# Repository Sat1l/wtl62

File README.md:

# wtl62

#### Hardware disclaimer
The folder structure is fucked up and probably wont be fixed as i see no reason for this.
Top case part (plate) is located in the bottom case part folder, and this one is located in the general pcb folder. Yeah.
There's also Willing To Live Better 62 inside, but this one proly wont' see a light of day as there prolly aint no interest in this design. Have fun.

#### firmware use guide
clone wtl62 folder to qmk_firmware/keyboards
#### Compiling
`qmk compile -kb WTL62 -km keymap`
- replace keymap with keymap you would like to compile. This repo contains only default keymap
#### Flashing default .hex file
[QMK Toolbox](https://github.com/qmk/qmk_toolbox) is the easiest way to do this. Short pins `gnd` and `rst` on yours MCU to reset
#### Using Vial
1. Flash `wtl62_via.hex` file to the keyboard
2. Open Vial
3. Go to File>Sideload VIA JSON...
4. Select `via.json` file
5. Voila! Now you can configure wtl62 using Vial

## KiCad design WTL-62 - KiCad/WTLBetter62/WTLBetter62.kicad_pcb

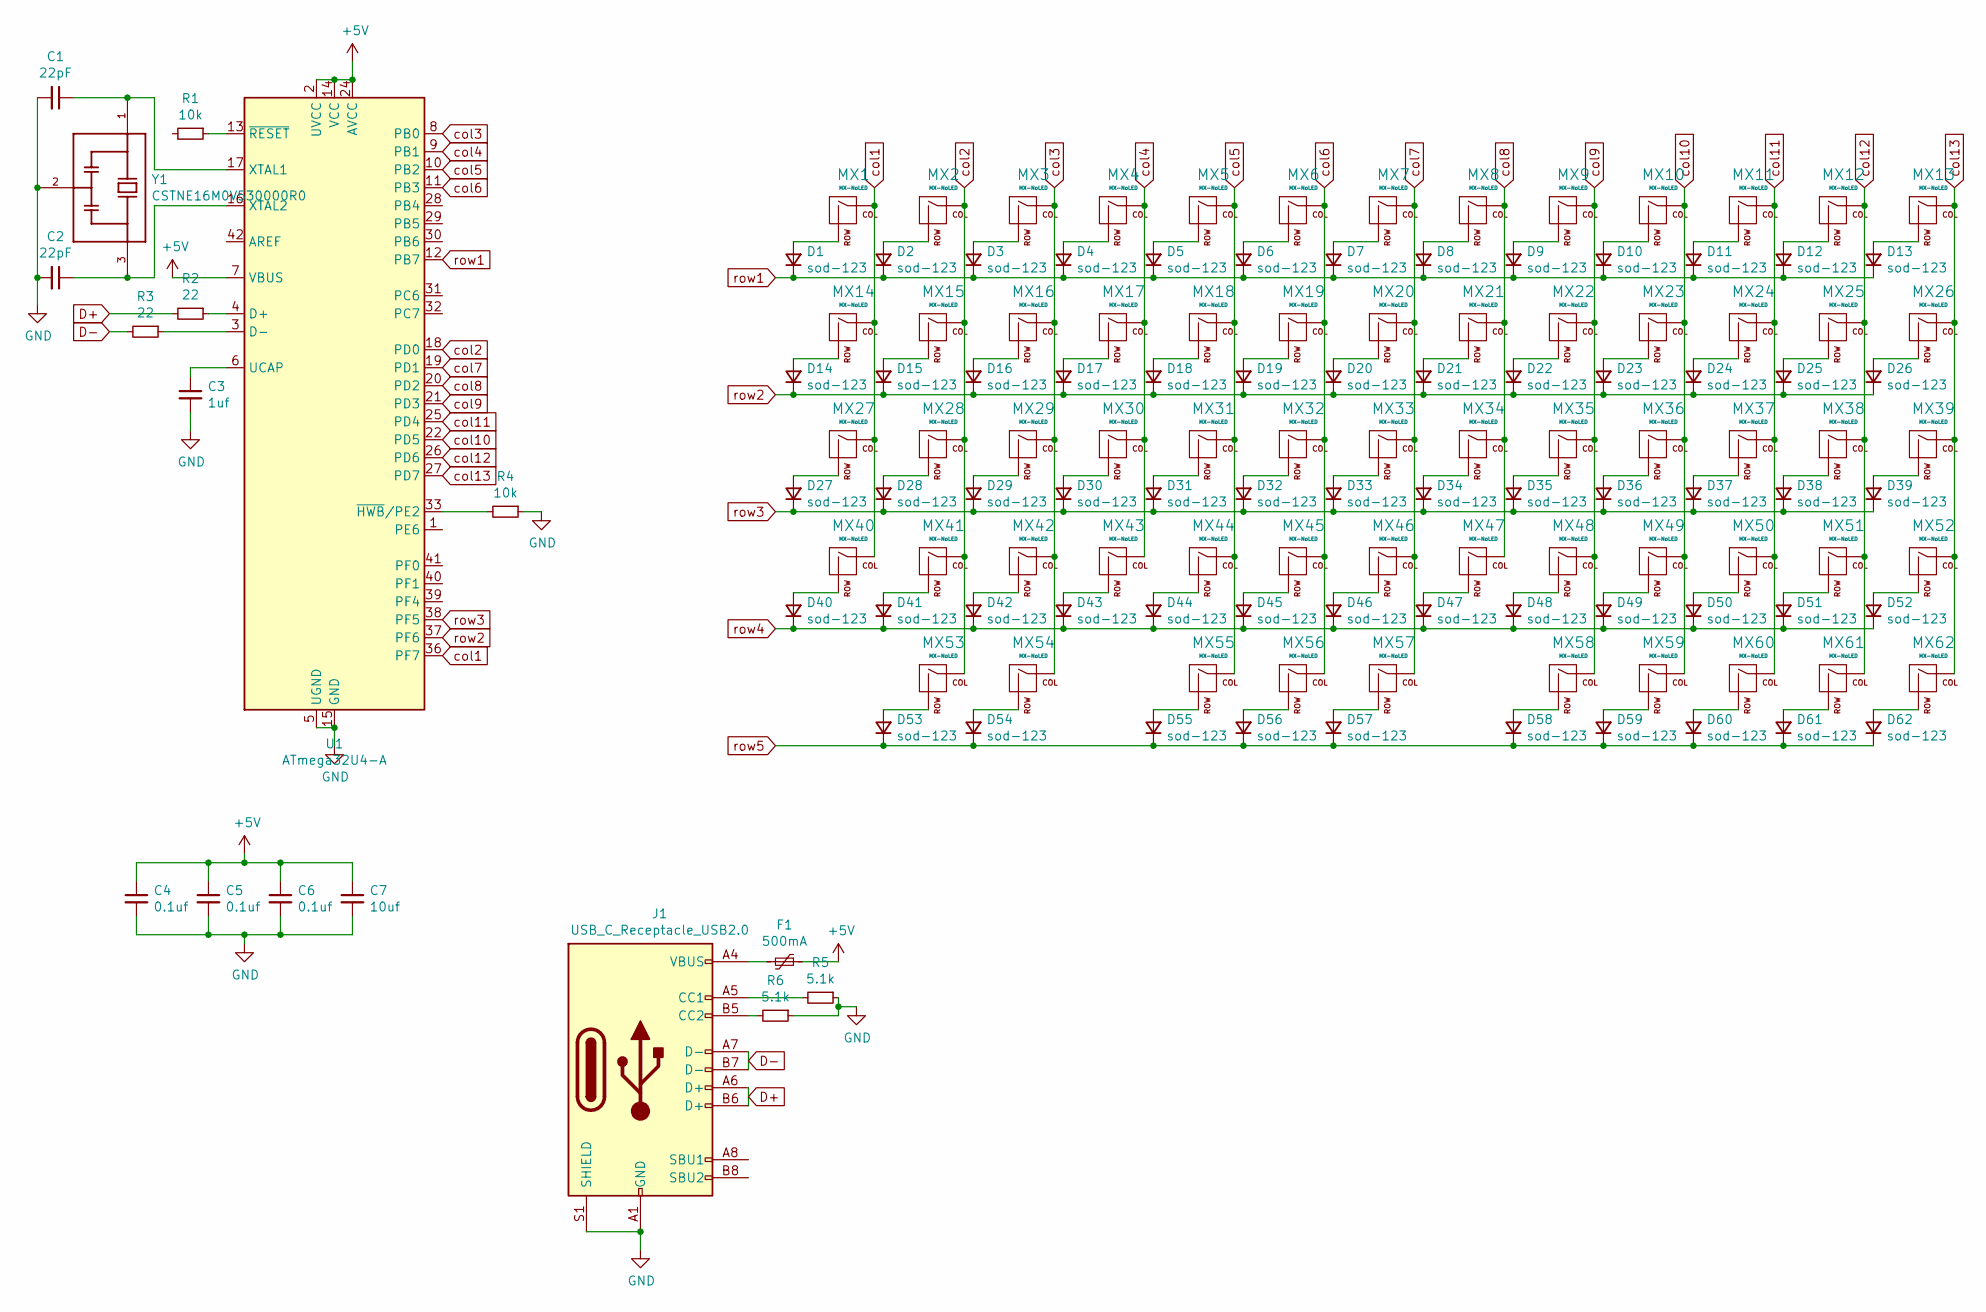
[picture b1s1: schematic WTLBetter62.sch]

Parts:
C1, C2: 22pF; C_0805_2012Metric
C3: 1uf; C_0805_2012Metric
C4, C5, C6: 0.1uf; C_0805_2012Metric
C7: 10uf; C_0805_2012Metric
D1, D2, D3, D4, D5, D6, D7, D8, D9, D10, D11, D12, D13, D14, D15, D16, D17, D18, D19, D20, D21, D22, D23, D24, D25, D26, D27, D28, D29, D30, D31, D32, D33, D34, D35, D36, D37, D38, D39, D40, D41, D42, D43, D44, D45, D46, D47, D48, D49, D50, D51, D52, D53, D54, D55, D56, D57, D58, D59, D60, D61, D62: sod-123; D3_SMD_v2
F1: 500mA; Fuse_1206_3216Metric
J1: USB_C_Receptacle_USB2.0; easyeda_C168688
MX1, MX2, MX3, MX4, MX5, MX6, MX7, MX8, MX9, MX10, MX11, MX12, MX13, MX14, MX15, MX16, MX17, MX18, MX19, MX20, MX21, MX22, MX23, MX24, MX25, MX26, MX27, MX28, MX29, MX30, MX31, MX32, MX33, MX34, MX35, MX36, MX37, MX38, MX39, MX40, MX41, MX42, MX43, MX44, MX45, MX46, MX47, MX48, MX49, MX50, MX51, MX52, MX53, MX54, MX55, MX56, MX57, MX58, MX59, MX60, MX61, MX62: MX-NoLED; CherryMX_Hotswap
R1, R4: 10k; R_0805_2012Metric
R2, R3: 22; R_0805_2012Metric
R5, R6: 5.1k; R_0805_2012Metric
U1: ATmega32U4-A; TQFP-44_10x10mm_P0.8mm
Y1: CSTNE16M0V530000R0; OSC_CSTNE16M0V530000R0; PARTREV JGC42-8853B

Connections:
+5V: C4.1, C5.1, C6.1, C7.1, F1.1, U1.2 (UVCC), U1.7 (VBUS), U1.14 (VCC), U1.24 (AVCC), U1.34 (VCC), U1.44 (AVCC)
D+: J1.A6 (D+), J1.B6 (D+), R2.2
D-: J1.A7 (D-), J1.B7 (D-), R3.2
GND: C1.2, C2.2, C3.2, C4.2, C5.2, C6.2, C7.2, J1.A1 (GND), J1.A12 (GND), J1.B1 (GND), J1.B12 (GND), J1.S1 (SHIELD), R4.1, R5.1, R6.1, U1.5 (UGND), U1.15 (GND), U1.23 (GND), U1.35 (GND), U1.43 (GND), Y1.2
unnamed: C1.1, U1.17 (XTAL1), Y1.1
unnamed: C2.1, U1.16 (XTAL2), Y1.3
unnamed: C3.1, U1.6 (UCAP)
unnamed: D1.2 (A), MX1.2 (ROW)
unnamed: D2.2 (A), MX2.2 (ROW)
unnamed: D3.2 (A), MX3.2 (ROW)
unnamed: D4.2 (A), MX4.2 (ROW)
unnamed: D5.2 (A), MX5.2 (ROW)
unnamed: D6.2 (A), MX6.2 (ROW)
unnamed: D7.2 (A), MX7.2 (ROW)
unnamed: D8.2 (A), MX8.2 (ROW)
unnamed: D9.2 (A), MX9.2 (ROW)
unnamed: D10.2 (A), MX10.2 (ROW)
unnamed: D11.2 (A), MX11.2 (ROW)
unnamed: D12.2 (A), MX12.2 (ROW)
unnamed: D13.2 (A), MX13.2 (ROW)
unnamed: D14.2 (A), MX14.2 (ROW)
unnamed: D15.2 (A), MX15.2 (ROW)
unnamed: D16.2 (A), MX16.2 (ROW)
unnamed: D17.2 (A), MX17.2 (ROW)
unnamed: D18.2 (A), MX18.2 (ROW)
unnamed: D19.2 (A), MX19.2 (ROW)
unnamed: D20.2 (A), MX20.2 (ROW)
unnamed: D21.2 (A), MX21.2 (ROW)
unnamed: D22.2 (A), MX22.2 (ROW)
unnamed: D23.2 (A), MX23.2 (ROW)
unnamed: D24.2 (A), MX24.2 (ROW)
unnamed: D25.2 (A), MX25.2 (ROW)
unnamed: D26.2 (A), MX26.2 (ROW)
unnamed: D27.2 (A), MX27.2 (ROW)
unnamed: D28.2 (A), MX28.2 (ROW)
unnamed: D29.2 (A), MX29.2 (ROW)
unnamed: D30.2 (A), MX30.2 (ROW)
unnamed: D31.2 (A), MX31.2 (ROW)
unnamed: D32.2 (A), MX32.2 (ROW)
unnamed: D33.2 (A), MX33.2 (ROW)
unnamed: D34.2 (A), MX34.2 (ROW)
unnamed: D35.2 (A), MX35.2 (ROW)
unnamed: D36.2 (A), MX36.2 (ROW)
unnamed: D37.2 (A), MX37.2 (ROW)
unnamed: D38.2 (A), MX38.2 (ROW)
unnamed: D39.2 (A), MX39.2 (ROW)
unnamed: D40.2 (A), MX40.2 (ROW)
unnamed: D41.2 (A), MX41.2 (ROW)
unnamed: D42.2 (A), MX42.2 (ROW)
unnamed: D43.2 (A), MX43.2 (ROW)
unnamed: D44.2 (A), MX44.2 (ROW)
unnamed: D45.2 (A), MX45.2 (ROW)
unnamed: D46.2 (A), MX46.2 (ROW)
unnamed: D47.2 (A), MX47.2 (ROW)
unnamed: D48.2 (A), MX48.2 (ROW)
unnamed: D49.2 (A), MX49.2 (ROW)
unnamed: D50.2 (A), MX50.2 (ROW)
unnamed: D51.2 (A), MX51.2 (ROW)
unnamed: D52.2 (A), MX52.2 (ROW)
unnamed: D53.2 (A), MX53.2 (ROW)
unnamed: D54.2 (A), MX54.2 (ROW)
unnamed: D55.2 (A), MX55.2 (ROW)
unnamed: D56.2 (A), MX56.2 (ROW)
unnamed: D57.2 (A), MX57.2 (ROW)
unnamed: D58.2 (A), MX58.2 (ROW)
unnamed: D59.2 (A), MX59.2 (ROW)
unnamed: D60.2 (A), MX60.2 (ROW)
unnamed: D61.2 (A), MX61.2 (ROW)
unnamed: D62.2 (A), MX62.2 (ROW)
unnamed: F1.2, J1.A4 (VBUS), J1.A9 (VBUS), J1.B4 (VBUS), J1.B9 (VBUS)
unnamed: J1.A5 (CC1), R5.2
unnamed: J1.B5 (CC2), R6.2
unnamed: R1.1, U1.13 (~RESET)
unnamed: R2.1, U1.4 (D+)
unnamed: R3.1, U1.3 (D-)
unnamed: R4.2, U1.33 (~HWB~/PE2)
col1: MX1.1 (COL), MX14.1 (COL), MX27.1 (COL), MX40.1 (COL), U1.36 (PF7)
col2: MX2.1 (COL), MX15.1 (COL), MX28.1 (COL), MX41.1 (COL), MX53.1 (COL), U1.18 (PD0)
col3: MX3.1 (COL), MX16.1 (COL), MX29.1 (COL), MX42.1 (COL), MX54.1 (COL), U1.8 (PB0)
col4: MX4.1 (COL), MX17.1 (COL), MX30.1 (COL), MX43.1 (COL), U1.9 (PB1)
col5: MX5.1 (COL), MX18.1 (COL), MX31.1 (COL), MX44.1 (COL), MX55.1 (COL), U1.10 (PB2)
col6: MX6.1 (COL), MX19.1 (COL), MX32.1 (COL), MX45.1 (COL), MX56.1 (COL), U1.11 (PB3)
col7: MX7.1 (COL), MX20.1 (COL), MX33.1 (COL), MX46.1 (COL), MX57.1 (COL), U1.19 (PD1)
col8: MX8.1 (COL), MX21.1 (COL), MX34.1 (COL), MX47.1 (COL), U1.20 (PD2)
col9: MX9.1 (COL), MX22.1 (COL), MX35.1 (COL), MX48.1 (COL), MX58.1 (COL), U1.21 (PD3)
col10: MX10.1 (COL), MX23.1 (COL), MX36.1 (COL), MX49.1 (COL), MX59.1 (COL), U1.22 (PD5)
col11: MX11.1 (COL), MX24.1 (COL), MX37.1 (COL), MX50.1 (COL), MX60.1 (COL), U1.25 (PD4)
col12: MX12.1 (COL), MX25.1 (COL), MX38.1 (COL), MX51.1 (COL), MX61.1 (COL), U1.26 (PD6)
col13: MX13.1 (COL), MX26.1 (COL), MX39.1 (COL), MX52.1 (COL), MX62.1 (COL), U1.27 (PD7)
row1: D1.1 (K), D2.1 (K), D3.1 (K), D4.1 (K), D5.1 (K), D6.1 (K), D7.1 (K), D8.1 (K), D9.1 (K), D10.1 (K), D11.1 (K), D12.1 (K), D13.1 (K), U1.12 (PB7)
row2: D14.1 (K), D15.1 (K), D16.1 (K), D17.1 (K), D18.1 (K), D19.1 (K), D20.1 (K), D21.1 (K), D22.1 (K), D23.1 (K), D24.1 (K), D25.1 (K), D26.1 (K), U1.37 (PF6)
row3: D27.1 (K), D28.1 (K), D29.1 (K), D30.1 (K), D31.1 (K), D32.1 (K), D33.1 (K), D34.1 (K), D35.1 (K), D36.1 (K), D37.1 (K), D38.1 (K), D39.1 (K), U1.38 (PF5)
row4: D40.1 (K), D41.1 (K), D42.1 (K), D43.1 (K), D44.1 (K), D45.1 (K), D46.1 (K), D47.1 (K), D48.1 (K), D49.1 (K), D50.1 (K), D51.1 (K), D52.1 (K)
row5: D53.1 (K), D54.1 (K), D55.1 (K), D56.1 (K), D57.1 (K), D58.1 (K), D59.1 (K), D60.1 (K), D61.1 (K), D62.1 (K)

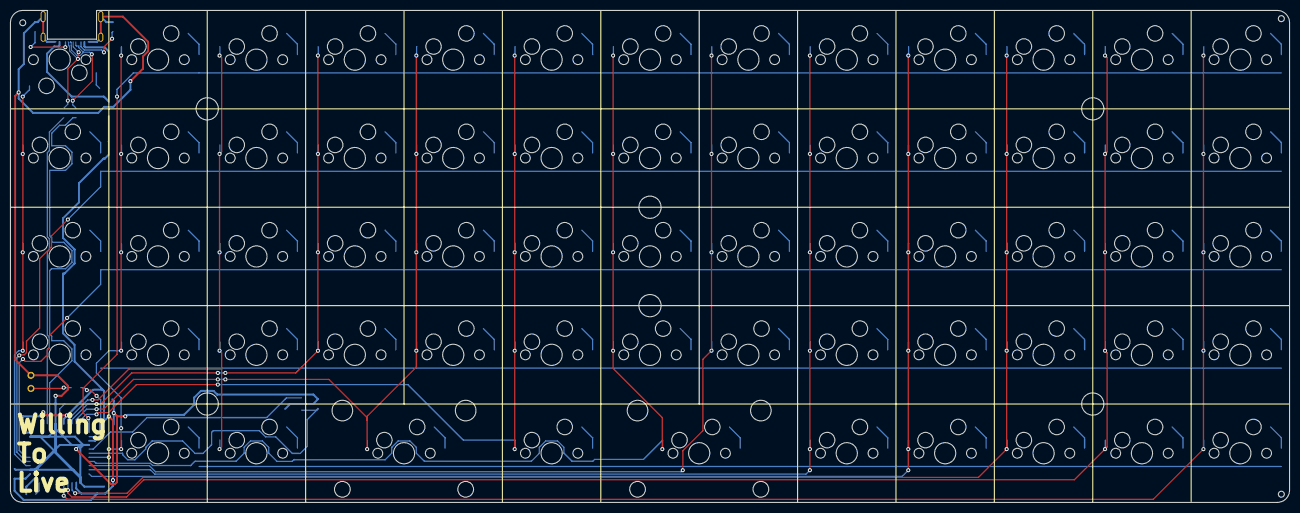
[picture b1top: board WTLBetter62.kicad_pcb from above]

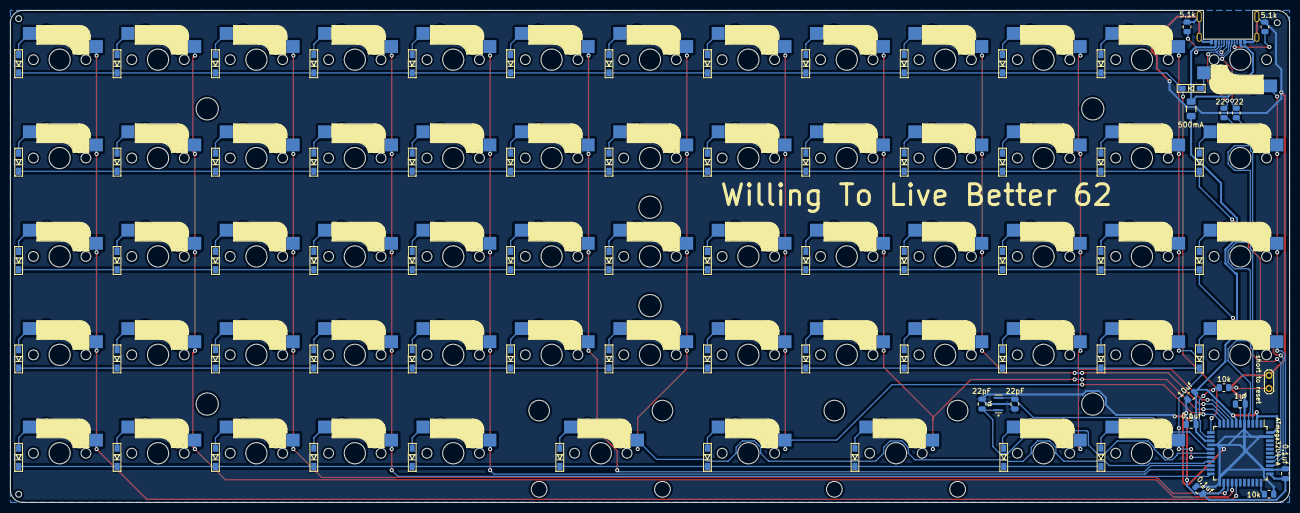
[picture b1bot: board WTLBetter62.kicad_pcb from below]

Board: 2 copper layers, 247.7 x 95.3 mm, 147 parts (79 on the bottom side), 94 nets.

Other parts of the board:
Ref**: Val**; M2_HOLE_v2
Ref**#2, Ref**#3, Ref**#4, Ref**#5, Ref**#6: Val**; M2_HOLE_v2

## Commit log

2022-01-04 ¯\_(ツ)_/¯
2022-01-04 Added via support
2023-07-04 Open sourced the KiCad design
2023-11-29 NOW FOR REAL ADDED KICAD FILES
2023-11-29 hooray
2023-11-29 Revert "hooray"
    This reverts commit 43bb25406b56d77f7ca5d514852bf4eac8a9435c.
2023-11-29 Revert "uh?"
    This reverts commit 8ecf971136036a2070c51811fbfc9717efea2e1c.
2023-11-29 Revert "NOW FOR REAL ADDED KICAD FILES"
    This reverts commit faa8c233870fdadf60d61d6ff53c29565a21c0cd.
2023-11-29 NOW 4REAL ADDED THE PCB FILES
